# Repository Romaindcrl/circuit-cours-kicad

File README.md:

# Circuit cours — KiCad

Projet de circuit électronique alimenté en 5 V, avec un 74HC14, un registre à décalage 74HC595 et un amplificateur audio LM386. Le schéma comprend trois résistances variables, des LED et une sortie pour haut-parleur.

## État d’avancement

Faute de temps, nous n’avons pas pu terminer la soudure de la breadboard finale.

## Fichiers du projet

| Fichier | Contenu |
| --- | --- |
| [Circuit cours.kicad_pro](Circuit%20cours.kicad_pro) | Réglages du projet |
| [Circuit cours.kicad_sch](Circuit%20cours.kicad_sch) | Schéma électrique |
| [Circuit cours.kicad_pcb](Circuit%20cours.kicad_pcb) | Implantation et routage du PCB |
| [apercus/](apercus/) | Schéma et PCB au format SVG |
| [medias/](medias/) | Photos du montage, schéma manuscrit et vidéo |

## Ouvrir avec KiCad

1. Télécharger le dépôt avec **Code → Download ZIP**, puis extraire l’archive, ou cloner le dépôt :

   ```sh
   git clone https://github.com/Romaindcrl/circuit-cours-kicad.git
   ```

2. Avec **KiCad 10**, ouvrir `Circuit cours.kicad_pro`.
3. Ouvrir le schéma ou l’éditeur de PCB depuis le gestionnaire de projet.

Les trois fichiers KiCad proviennent du projet fourni et sont conservés sans modification. Leur lecture et les exports ont été vérifiés avec KiCad 10.0.6 ; cette vérification ne constitue pas un test du montage physique.

## Aperçus

### Schéma électrique

### Implantation et routage

Vue de dessus des couches de cuivre avant et arrière et de la sérigraphie avant.

## Photos et vidéo du montage

[Voir ou télécharger la vidéo du montage, avec le son](medias/demonstration.mp4) — environ 48 secondes, au format MP4.

### Montage sur breadboard

### Schéma manuscrit

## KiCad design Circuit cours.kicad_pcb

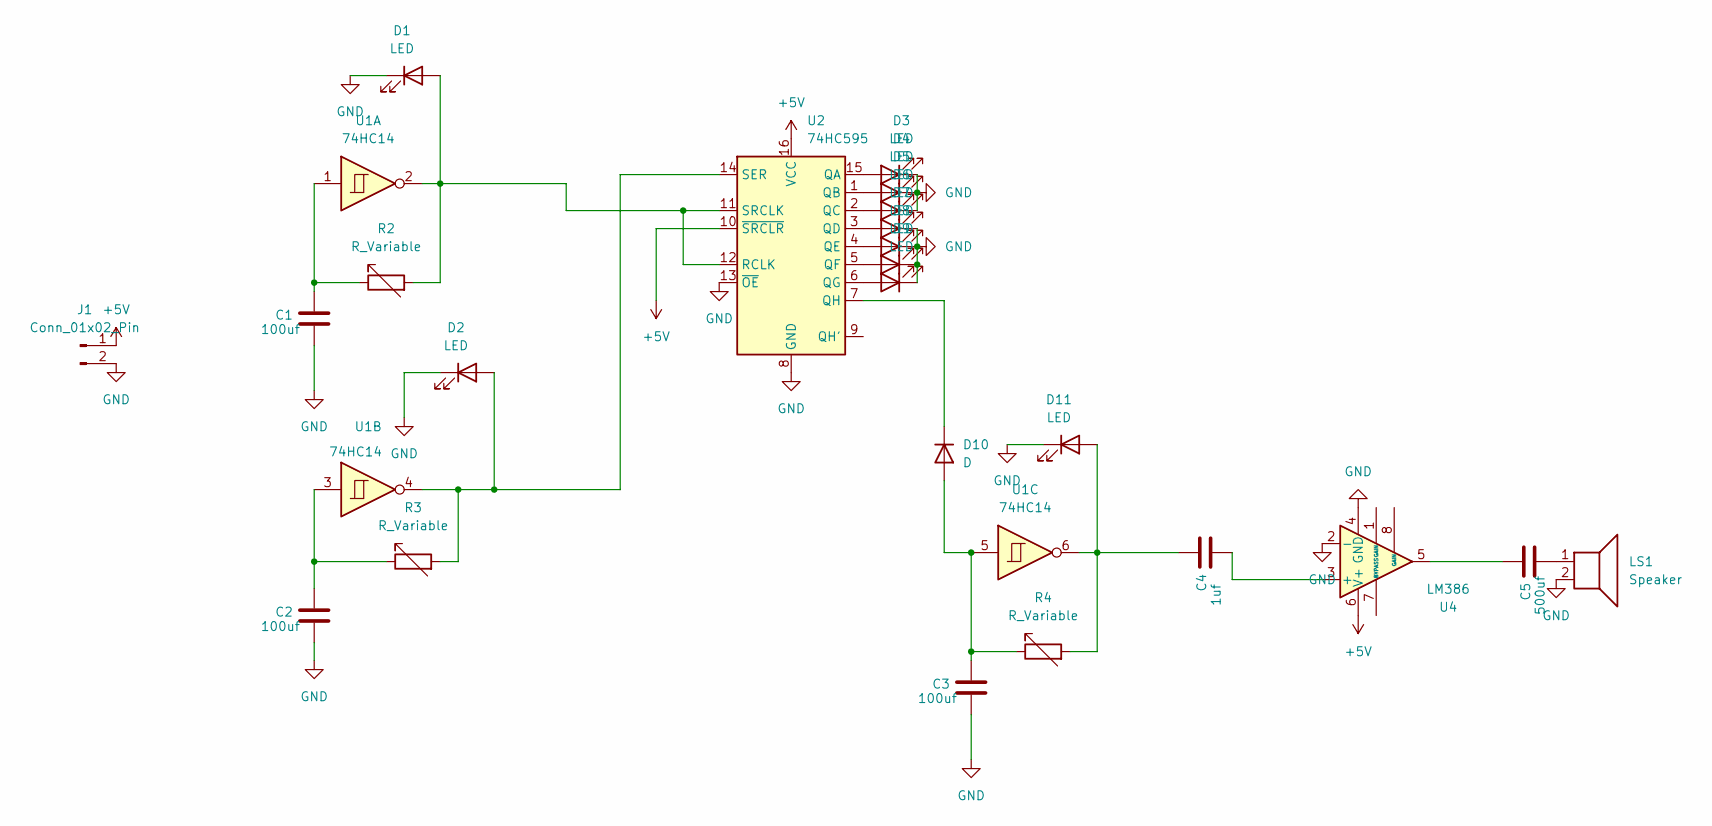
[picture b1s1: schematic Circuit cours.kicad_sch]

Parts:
C1, C2, C3: 100uf; CP_Radial_D6.3mm_P2.50mm
C4: 1uf; CP_Radial_D6.3mm_P2.50mm
C5: 500uf; CP_Radial_D6.3mm_P2.50mm
D1, D2, D3, D4, D5, D6, D7, D8, D9, D11: LED; LED_D5.0mm
D10: D; D_DO-35_SOD27_P7.62mm_Horizontal
J1: Conn_01x02_Pin; PinHeader_1x02_P1.00mm_Horizontal
LS1: Speaker; TerminalBlock_Phoenix_MKDS-1,5-2_1x02_P5.00mm_Horizontal
R2, R3, R4: R_Variable; Potentiometer_ACP_CA6-H2,5_Horizontal
U1: 74HC14; CERDIP-14_W7.62mm_SideBrazed
U2: 74HC595; CERDIP-16_W7.62mm_SideBrazed
U4: LM386; DIP-8_W7.62mm

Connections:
+5V: J1.1, U2.10 (~SRCLR), U2.16 (VCC), U4.6 (V+)
GND: C1.2, C2.2, C3.2, D1.1 (K), D2.1 (K), D3.1 (K), D4.1 (K), D5.1 (K), D6.1 (K), D7.1 (K), D8.1 (K), D9.1 (K), D11.1 (K), J1.2, LS1.2, U2.8 (GND), U2.13 (~OE), U4.2 (-), U4.4 (GND)
unnamed: C1.1, R2.1, U1.1
unnamed: C2.1, R3.1, U1.3
unnamed: C5.1, U4.5
unnamed: C5.2, LS1.1
unnamed: D1.2 (A), R2.2, U1.2, U2.11 (SRCLK), U2.12 (RCLK)
unnamed: D2.2 (A), R3.2, U1.4, U2.14 (SER)
unnamed: D3.2 (A), U2.15 (QA)
unnamed: D4.2 (A), U2.1 (QB)
unnamed: D5.2 (A), U2.2 (QC)
unnamed: D6.2 (A), U2.3 (QD)
unnamed: D7.2 (A), U2.4 (QE)
unnamed: D8.2 (A), U2.5 (QF)
unnamed: D9.2 (A), U2.6 (QG)
unnamed: C3.1, D10.2 (A), R4.1, U1.5
unnamed: D10.1 (K), U2.7 (QH)
unnamed: C4.1, D11.2 (A), R4.2, U1.6
unnamed: C4.2, U4.3 (+)

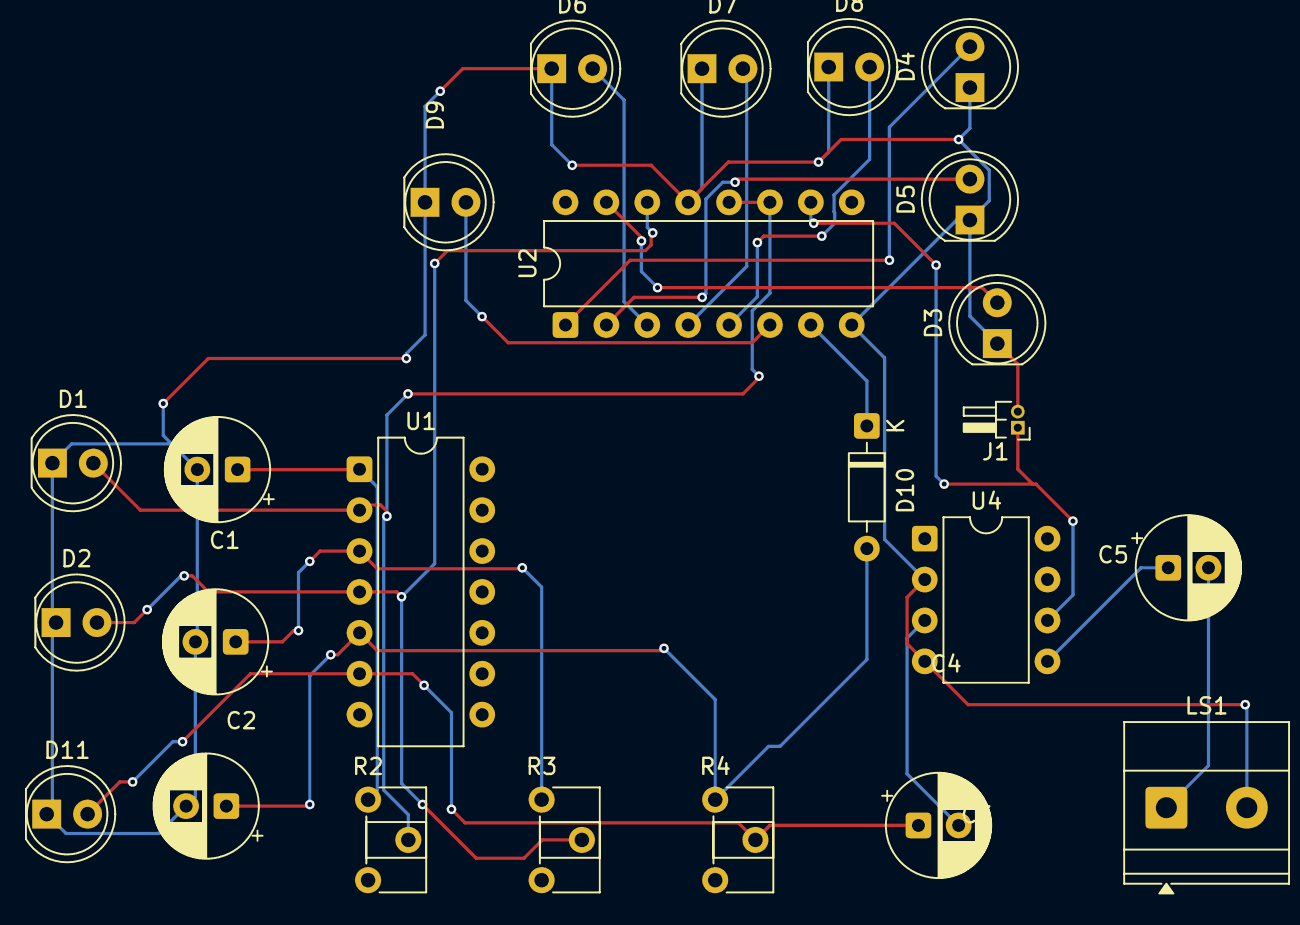
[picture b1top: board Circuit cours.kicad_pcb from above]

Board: 2 copper layers, 24 parts (0 on the bottom side), 19 nets.
